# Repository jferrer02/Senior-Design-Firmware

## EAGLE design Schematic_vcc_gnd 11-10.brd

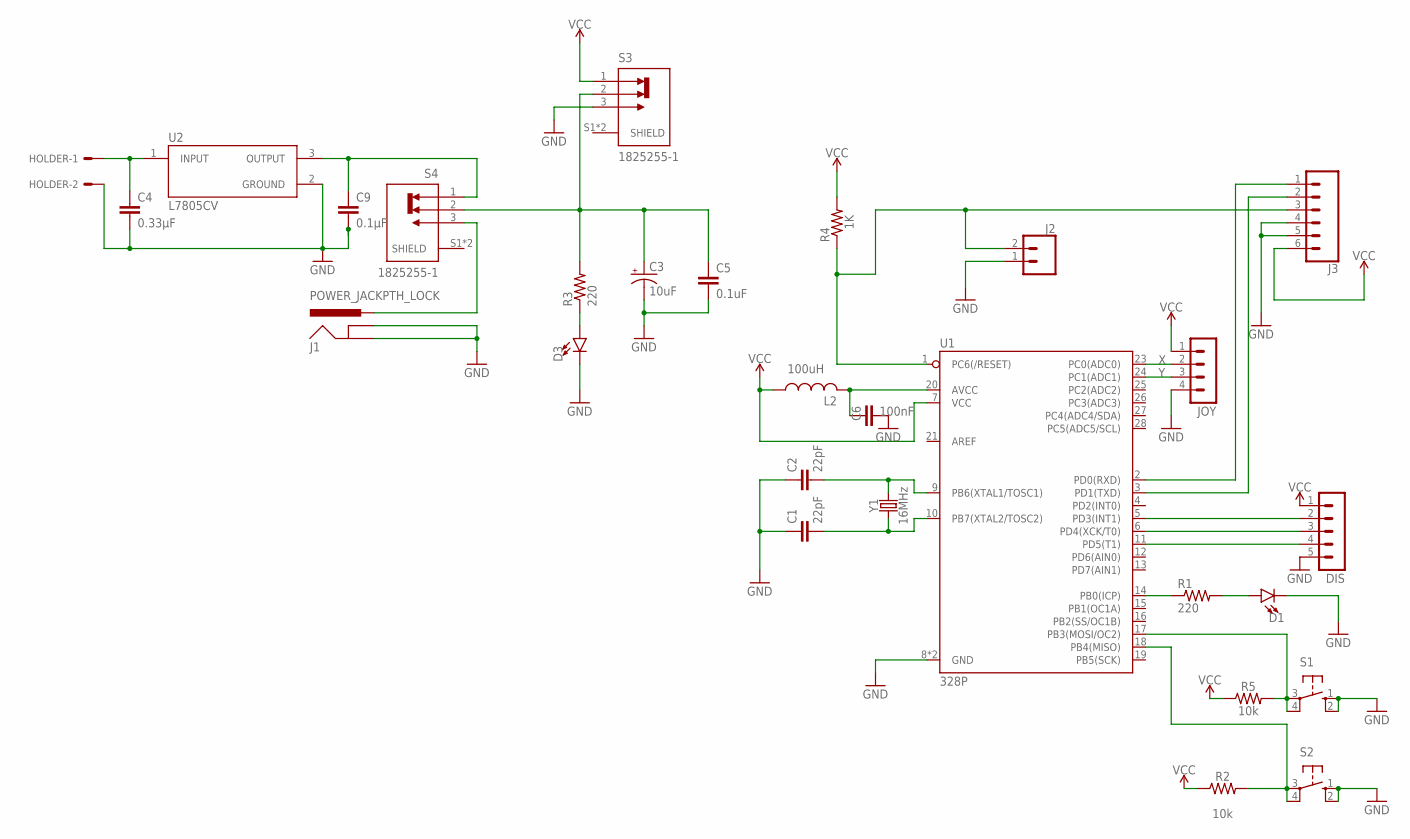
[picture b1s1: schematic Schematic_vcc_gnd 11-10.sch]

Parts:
C1, C2: 22pF; CAP-PTH-2.54
C3: 10uF; CPOL-RADIAL-2.5MM-5MM
C4: 0.33µF; C2.5-2
C5: 0.1uF; CAP-PTH-SMALL-KIT
C6: C2,5-3; C2.5-3
C9: 0.1µF; C2.5-2
D1, D3: LED3MM; LED_3MM
DIS: MA05-1
HOLDER: 22-23-2021; MPN Holder
J1: POWER_JACKPTH_LOCK; POWER_JACK_PTH_LOCK
J2: CONN_02; 1X02
J3: CONN_06SILK_FEMALE_PTH; 1X06
JOY: MA04-1
L2: L-US0204/5; 0204/5
R1, R3: 220; 0207/10
R2, R5: 10k; AXIAL-0.3
R4: 1K; 0207/10
S1, S2: 40-XX; B3F-40XX
S3, S4: 1825255-1; SW_1825255-1
U1: 328P; DIP28
U2: L7805CV; TO255P1040X460X1968-3
Y1: 16MHz; HC49US

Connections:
GND: C1.1, C2.1, C3.2 (-), C4.2, C5.2, C6.2, C9.2, D1.K (C), D3.K (C), DIS.5, HOLDER.2, J1.GND, J1.GNDBREAK, J2.1, J3.4, J3.5, JOY.4, S1.1 (S), S1.2 (S1), S2.1 (S), S2.2 (S1), S3.3, U1.8 (GND), U1.22 (GND), U2.2 (GROUND)
unnamed: J2.2, J3.3, R4.1, U1.1 (PC6(/RESET))
unnamed: D3.A, R3.1
unnamed: C2.2, U1.9 (PB6(XTAL1/TOSC1)), Y1.2
unnamed: C1.2, U1.10 (PB7(XTAL2/TOSC2)), Y1.1
unnamed: R1.1, U1.14 (PB0(ICP))
unnamed: D1.A, R1.2
unnamed: DIS.2, U1.5 (PD3(INT1))
unnamed: DIS.3, U1.6 (PD4(XCK/T0))
unnamed: J3.1, U1.2 (PD0(RXD))
unnamed: J3.2, U1.3 (PD1(TXD))
unnamed: C6.1, L2.2, U1.20 (AVCC)
unnamed: DIS.4, U1.11 (PD5(T1))
unnamed: R2.P$2 (2), S2.3, S2.4 (P1), U1.18 (PB4(MISO))
unnamed: R5.P$2 (2), S1.3, S1.4 (P1), U1.17 (PB3(MOSI/OC2))
unnamed: J1.PWR, S4.3
unnamed: C4.1, HOLDER.1, U2.1 (INPUT)
unnamed: C9.1, S4.1, U2.3 (OUTPUT)
unnamed: C3.1 (+), C5.1, R3.2, S3.2, S4.2
VCC: DIS.1, J3.6, JOY.1, L2.1, R2.P$1 (1), R4.2, R5.P$1 (1), S3.1, U1.7 (VCC)
X: JOY.2, U1.23 (PC0(ADC0))
Y: JOY.3, U1.24 (PC1(ADC1))

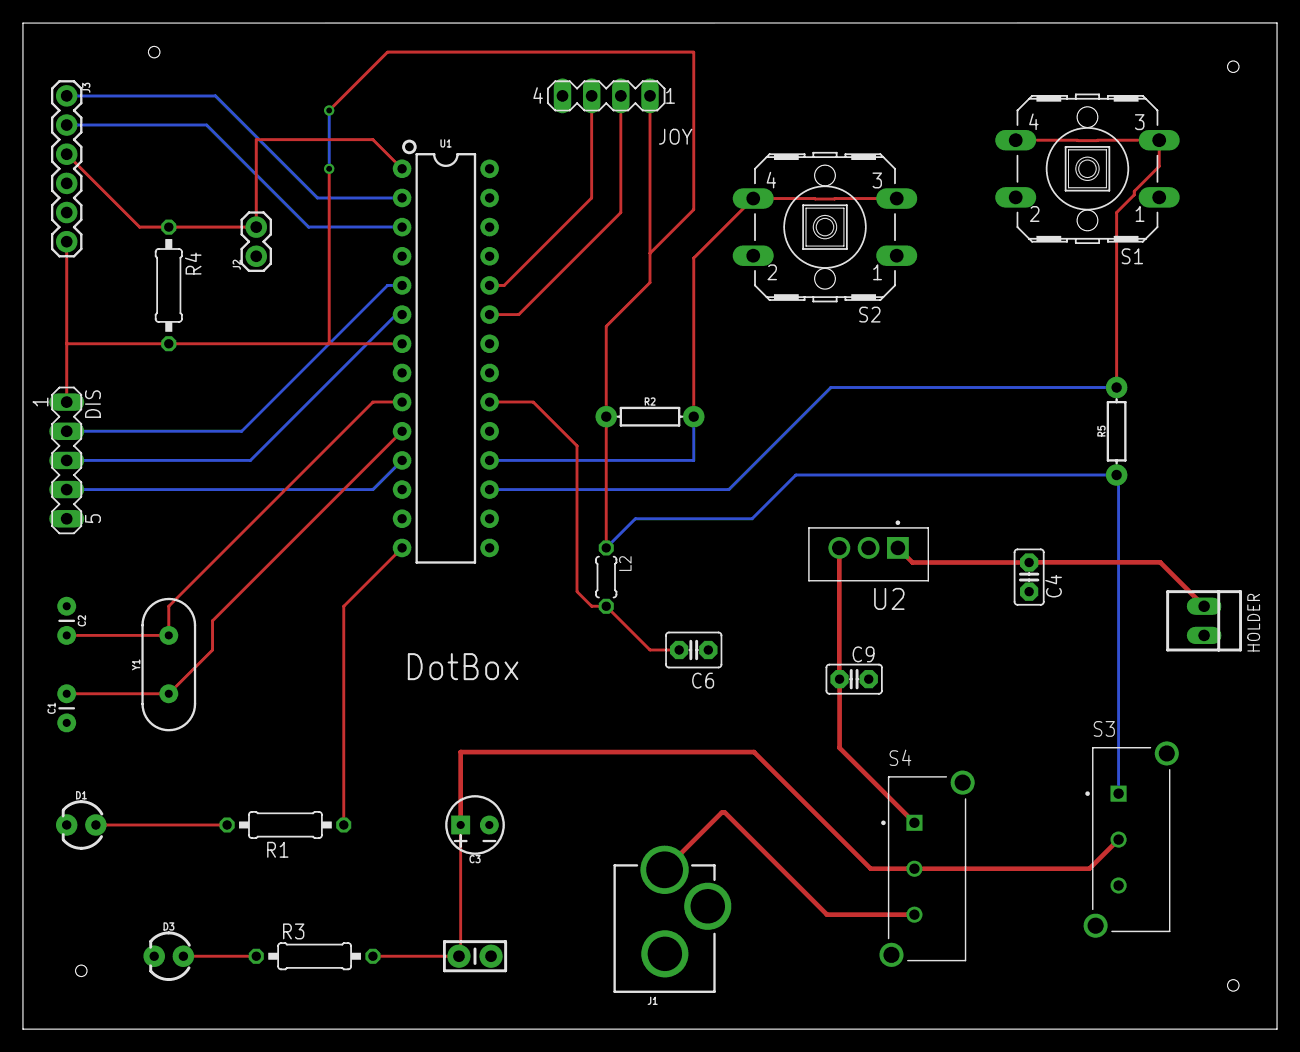
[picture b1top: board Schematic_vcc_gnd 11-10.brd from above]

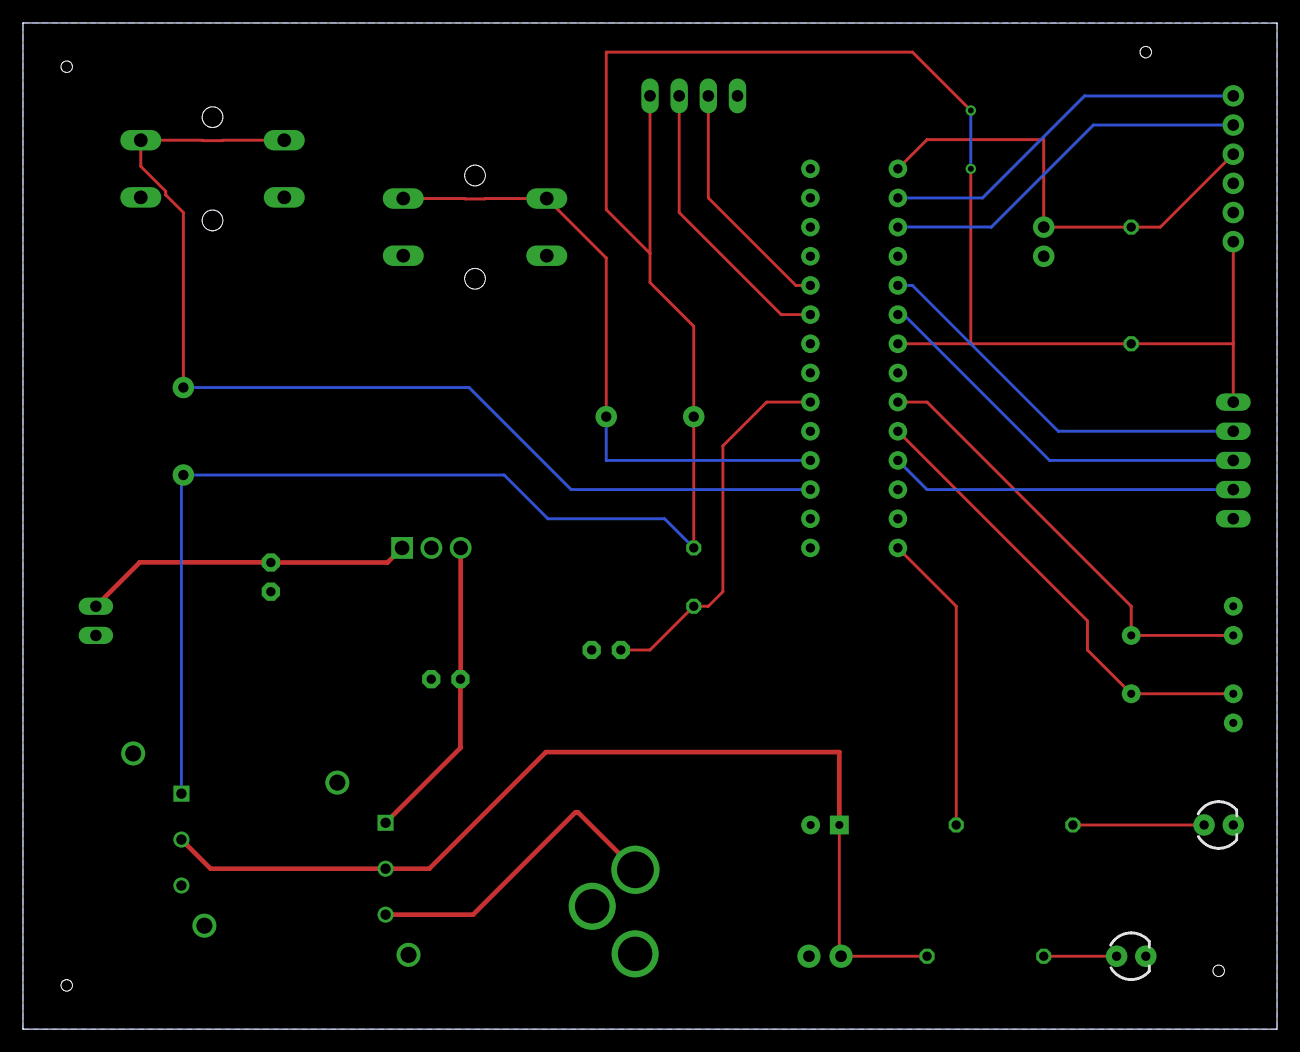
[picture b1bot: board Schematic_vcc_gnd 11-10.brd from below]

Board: 2 copper layers, 109.2 x 87.6 mm, 28 parts (2 on the bottom side), 22 nets.

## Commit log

2023-02-21 New repo for Senior Design Firmware
2023-02-21 updated to test whether file change happens on github
2023-02-21 brought back to normal
2023-02-21 Update main.ino
    Updating on GitHub and then pulling
2023-02-21 removed from repository
2023-02-21 Delete ~$Wiring.docx
    deleting a file
2023-02-21 Update main.ino
    removing a comment
2023-02-23 now working on a menu
2023-02-23 Made more changes to the menu
2023-02-23 main.ino is now in main directory
2023-02-23 main.ino in main directory
2023-02-23 commiting changes
2023-02-24 made more changes, now need to test if works.
2023-02-24 Add files via upload
    Eagle PCB schematic and board layout
2023-02-24 added a comment to main.ino
2023-02-24 made changes
2023-02-24 worked on game and made changes to menu
2023-02-27 made more changes
2023-03-03 Updating first game
2023-03-04 made more updates to Game 1
2023-03-09 Updated code
2023-03-09 Added more to Game1 - working on arrows that cross the screen.
2023-03-10 made more changes to Game1
2023-03-10 updating tolerances of joystick values
2023-03-10 ArduinoMaze game
    Currently can display the maze and allow the player to move.
    Contains several issues and bugs:
    1. The check for maze walls does not work for all wall, the player can clip through certain walls in the maze
    2. Player movement is limited and does not proceed past the Row 3 and Column 12
2023-03-10 Made changes to game1
2023-03-15 added a comment for the sake of merging
2023-03-17 Updated MazeGame
    Has an exit, and generates "You win" upon reaching the exit
2023-03-18 Made changes to menu and Game1()
2023-03-21 more changes to Game1
2023-03-23 hopefully this is a version that can be run
2023-03-30 Attempt to have both games in one program
2023-04-07 now using points and health, still needs more added though
2023-04-21 made a bunch of changes
2023-04-21 Updated maze game in maze
    Fixed the display of the maze game
2023-04-21 Updated main
    Updated the menu and changed the button to breakout of games to b_@
2023-04-28 more changes
2023-05-05 final push

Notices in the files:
parts and their libraries:
SparkFun-Capacitors: Licensing: Creative Commons ShareAlike 4.0 International - https://creativecommons.org/licenses/by-sa/4.0
